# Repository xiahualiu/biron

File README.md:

# biron

Biron is an open source soldering iron hardware based on Baxandall Oscillator. This is a homebrew project that I am doing during the free time at home.

## Software Requirements

* KiCAD v7.0.0 or above to view the schematic and PCB files.
* LTSpice 17.1.6.0 or above to view the SPICE simulation.

## Disclaimer

This is an open source project that involves high voltage and hot surfaces. You must have enough experience to build it in real life and wear PPE, I don't want people get hurt.

This project follows the Ti's [DAQ system requirements](https://www.ti.com/solution/data-acquisition-daq), the control system is fully galvanized isolated from the physical and power signals.

### Power isolation

I used a minimal push-pull converter for the DC/DC part:

### Sensor signal isolation

Sensor signals are amplifier through a TL082H (not practical in the real world because of the high Vos, you want Vos<100uV if possible). The signal is read by a RV1S9353A from Renesas.

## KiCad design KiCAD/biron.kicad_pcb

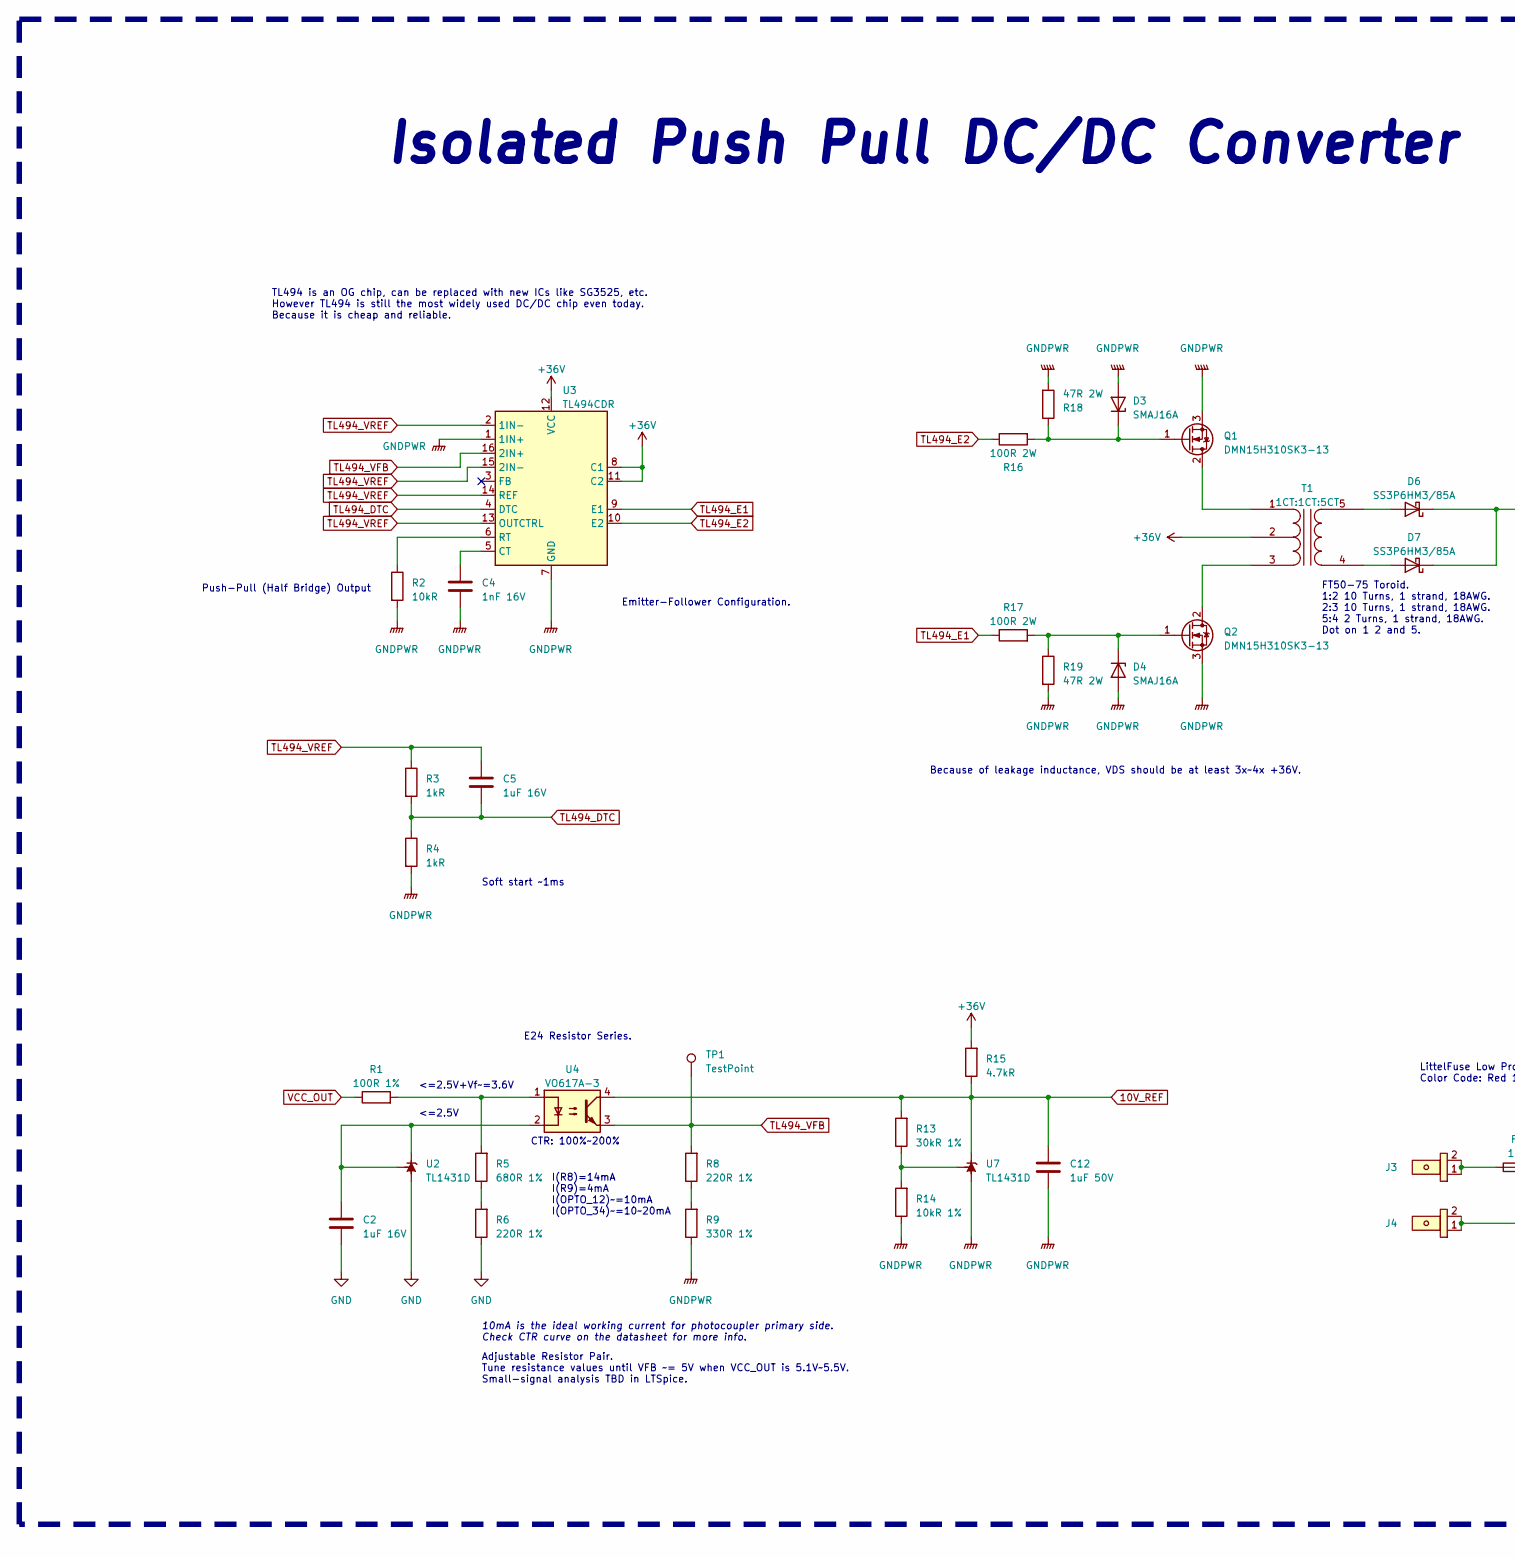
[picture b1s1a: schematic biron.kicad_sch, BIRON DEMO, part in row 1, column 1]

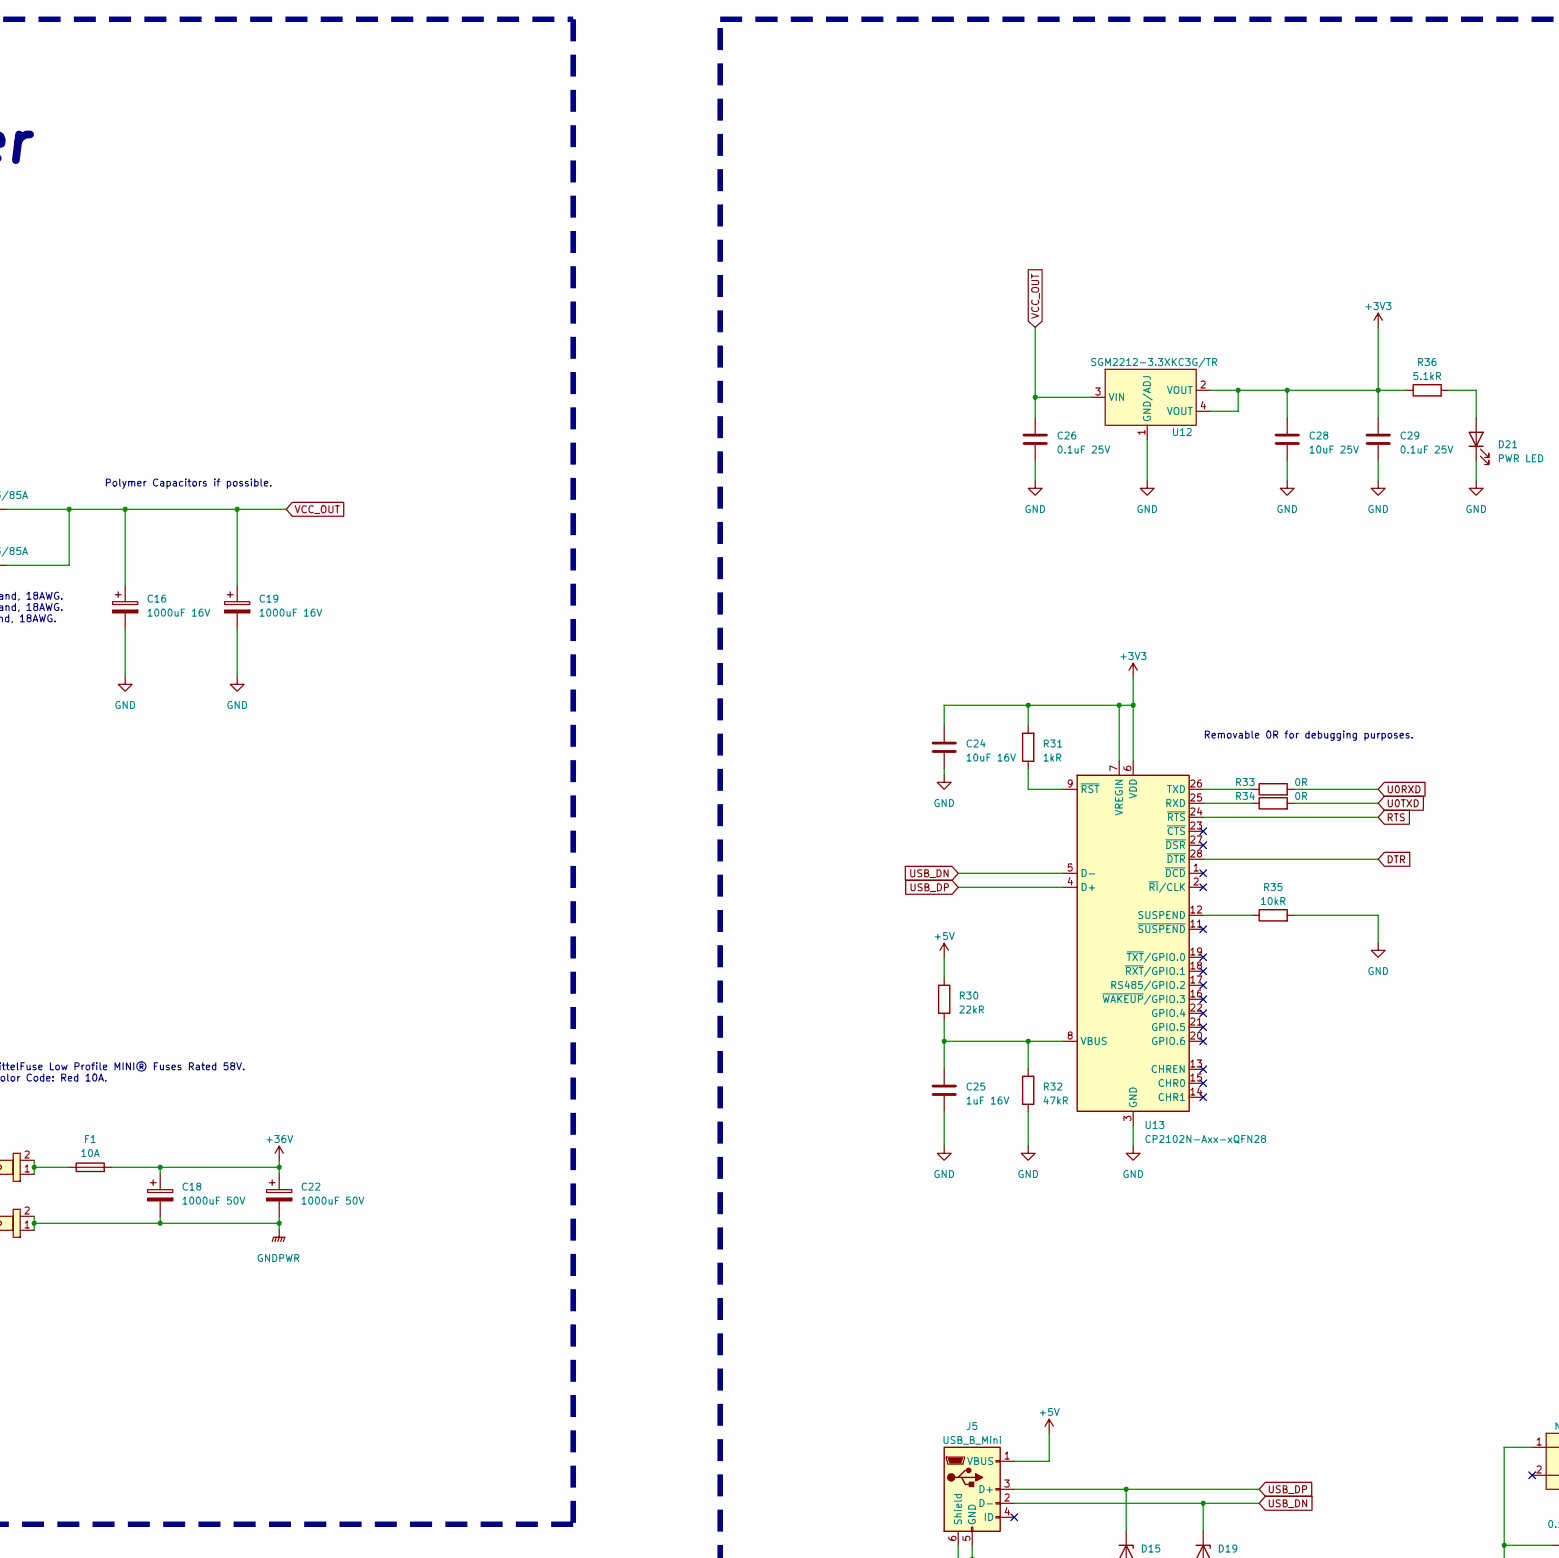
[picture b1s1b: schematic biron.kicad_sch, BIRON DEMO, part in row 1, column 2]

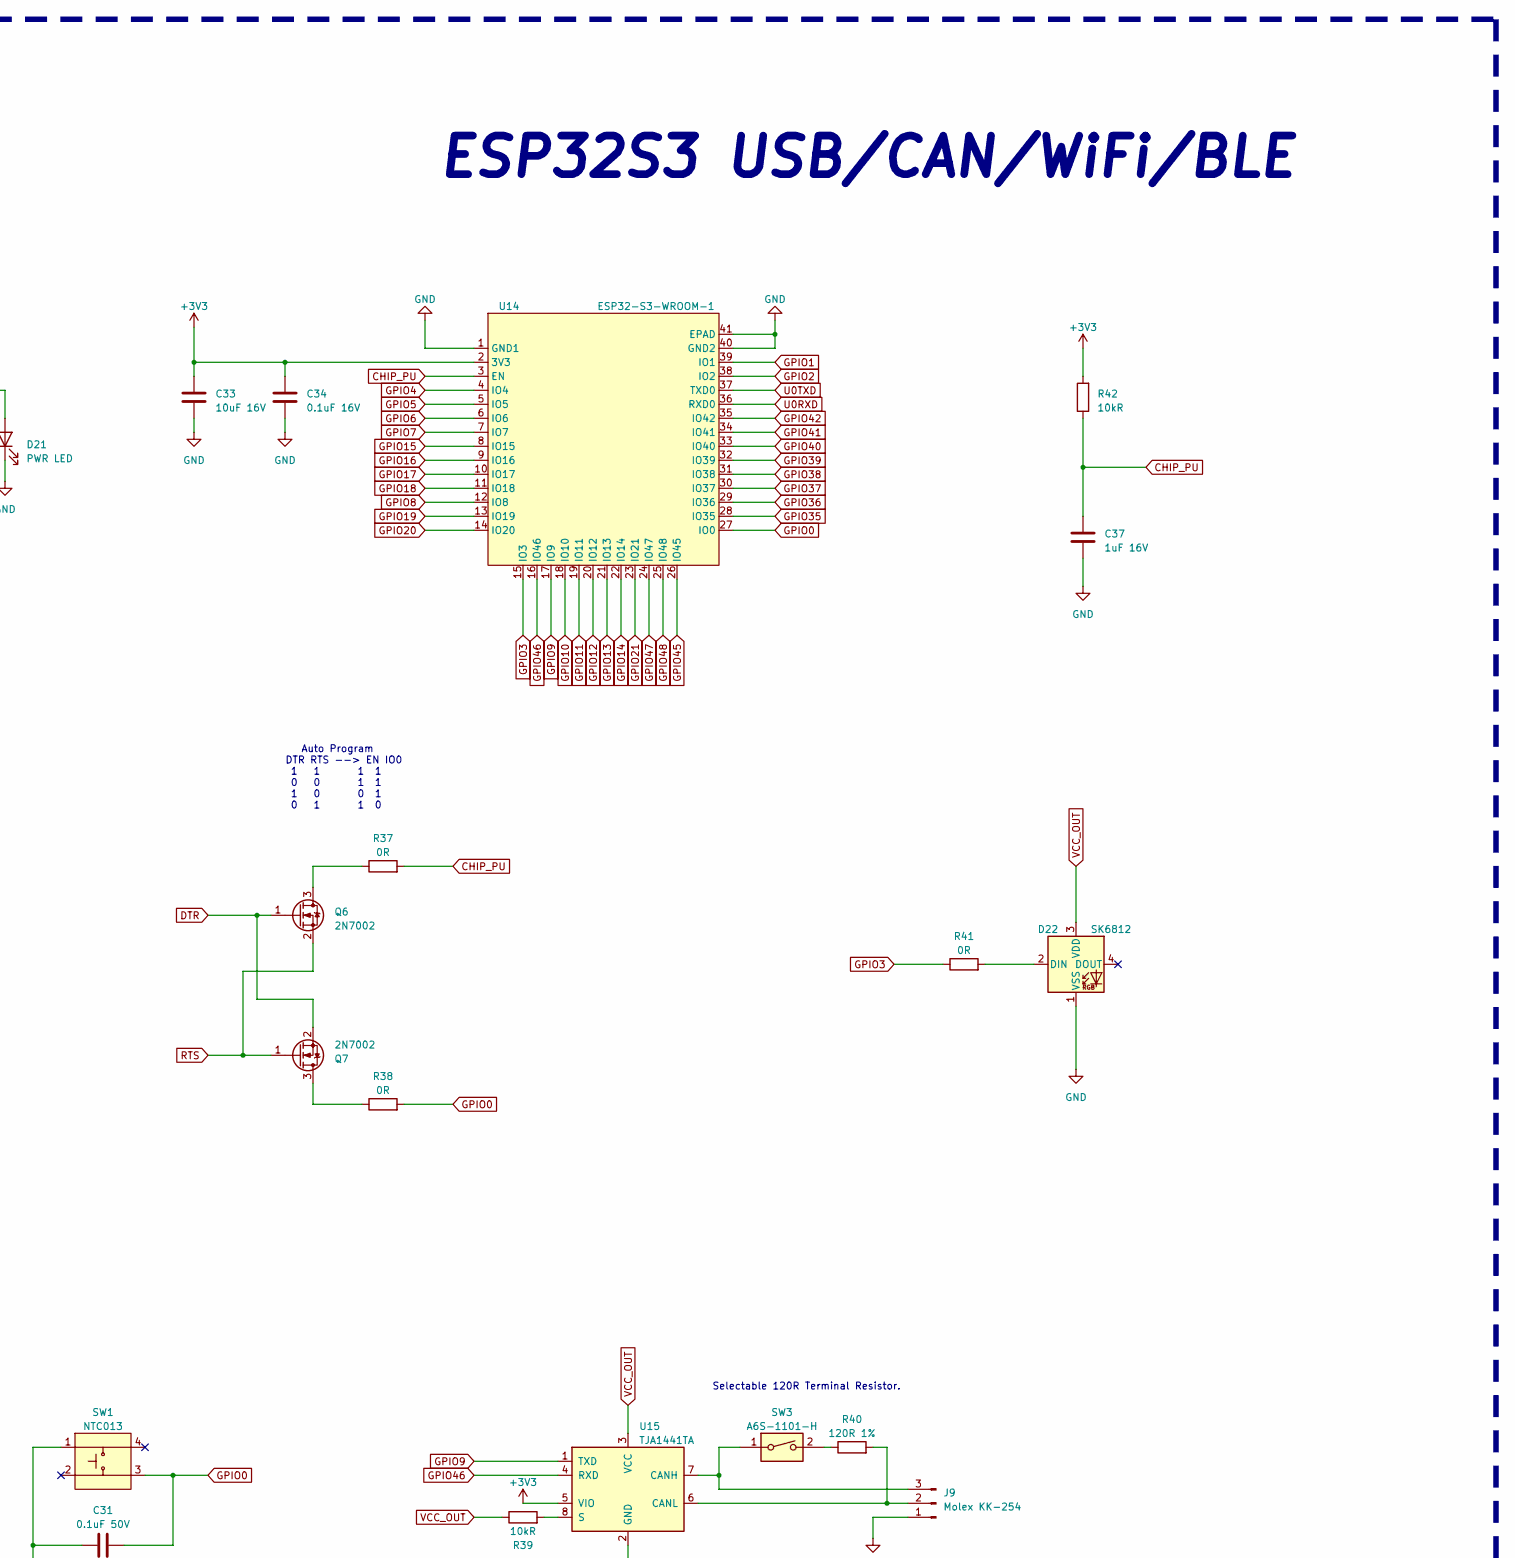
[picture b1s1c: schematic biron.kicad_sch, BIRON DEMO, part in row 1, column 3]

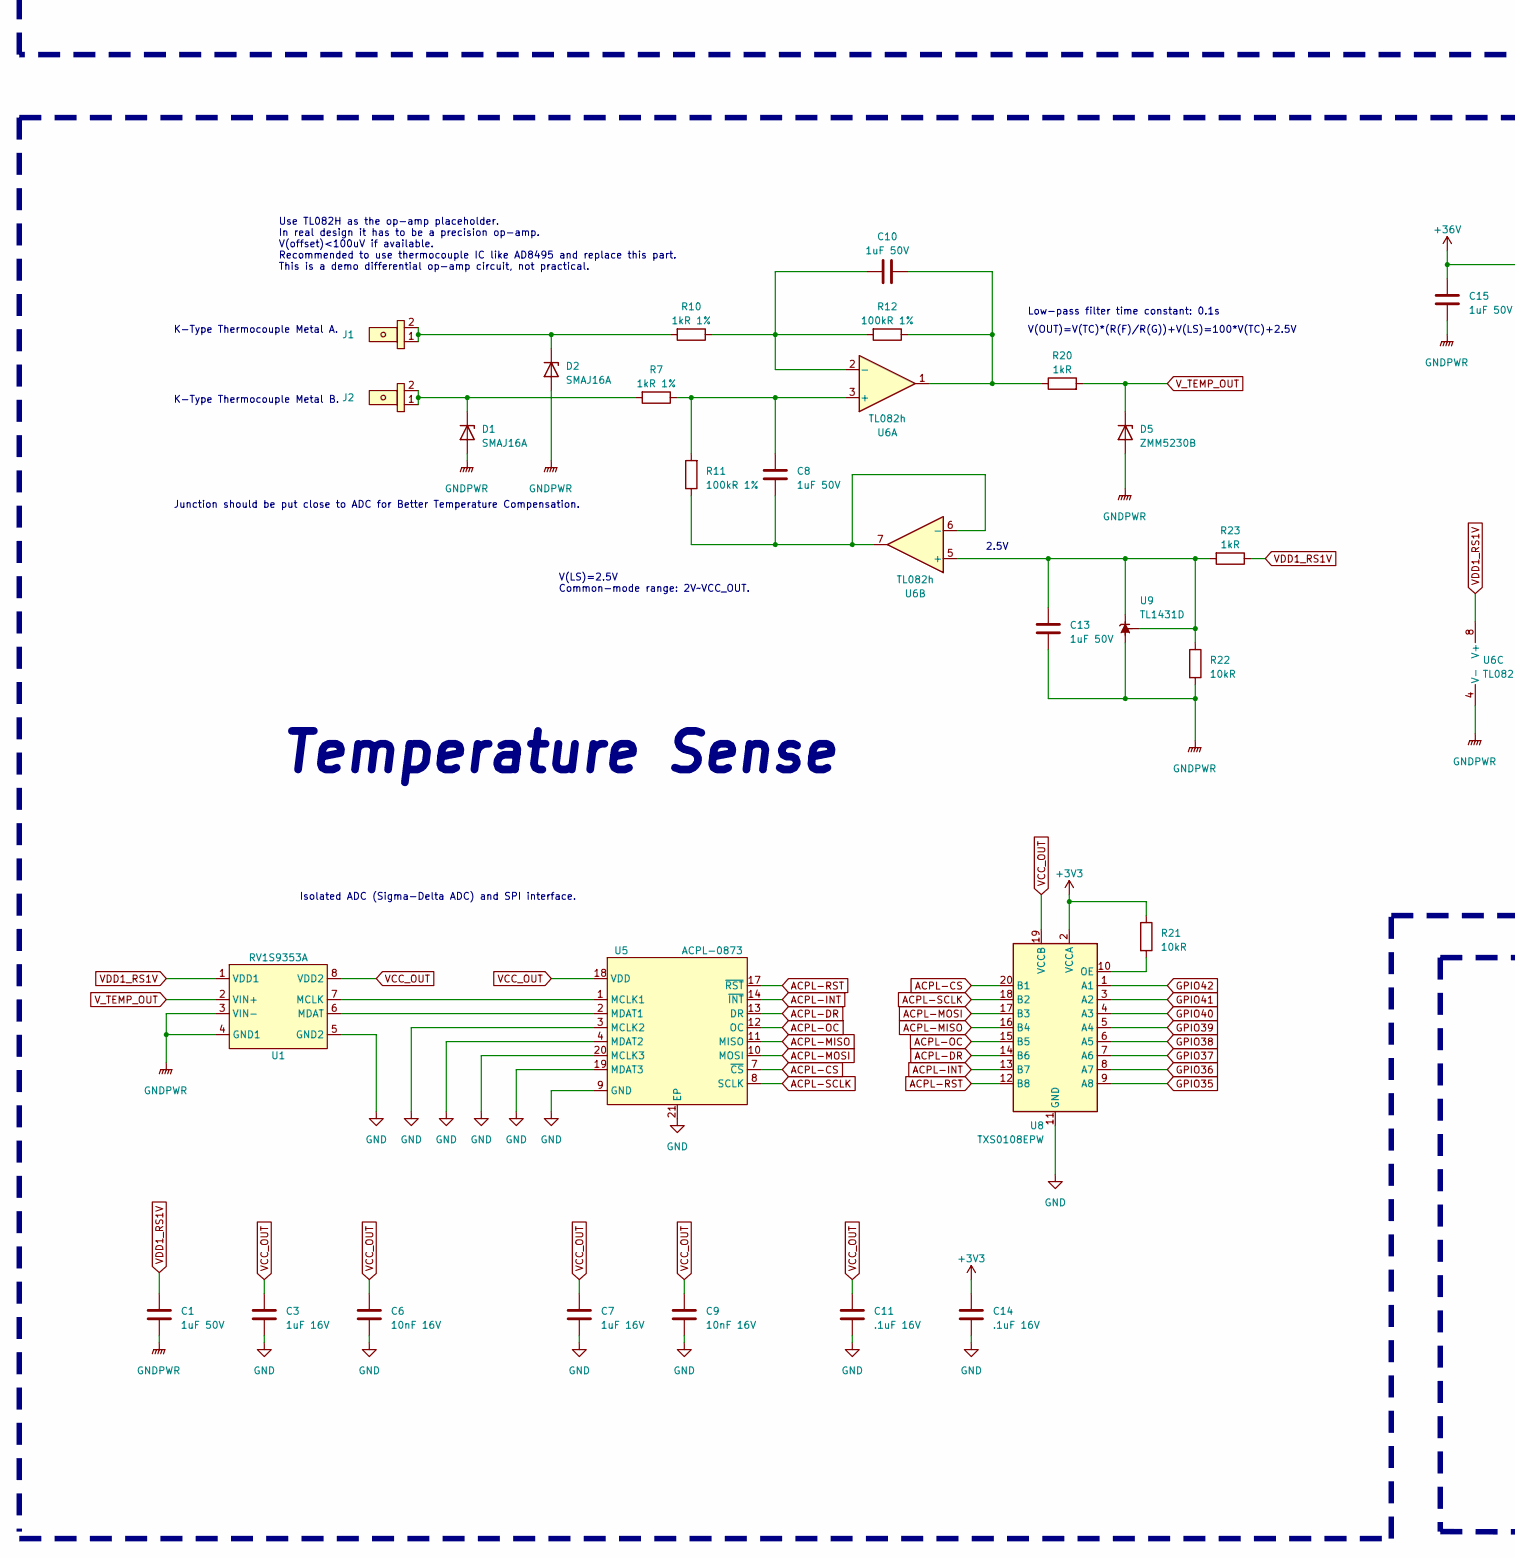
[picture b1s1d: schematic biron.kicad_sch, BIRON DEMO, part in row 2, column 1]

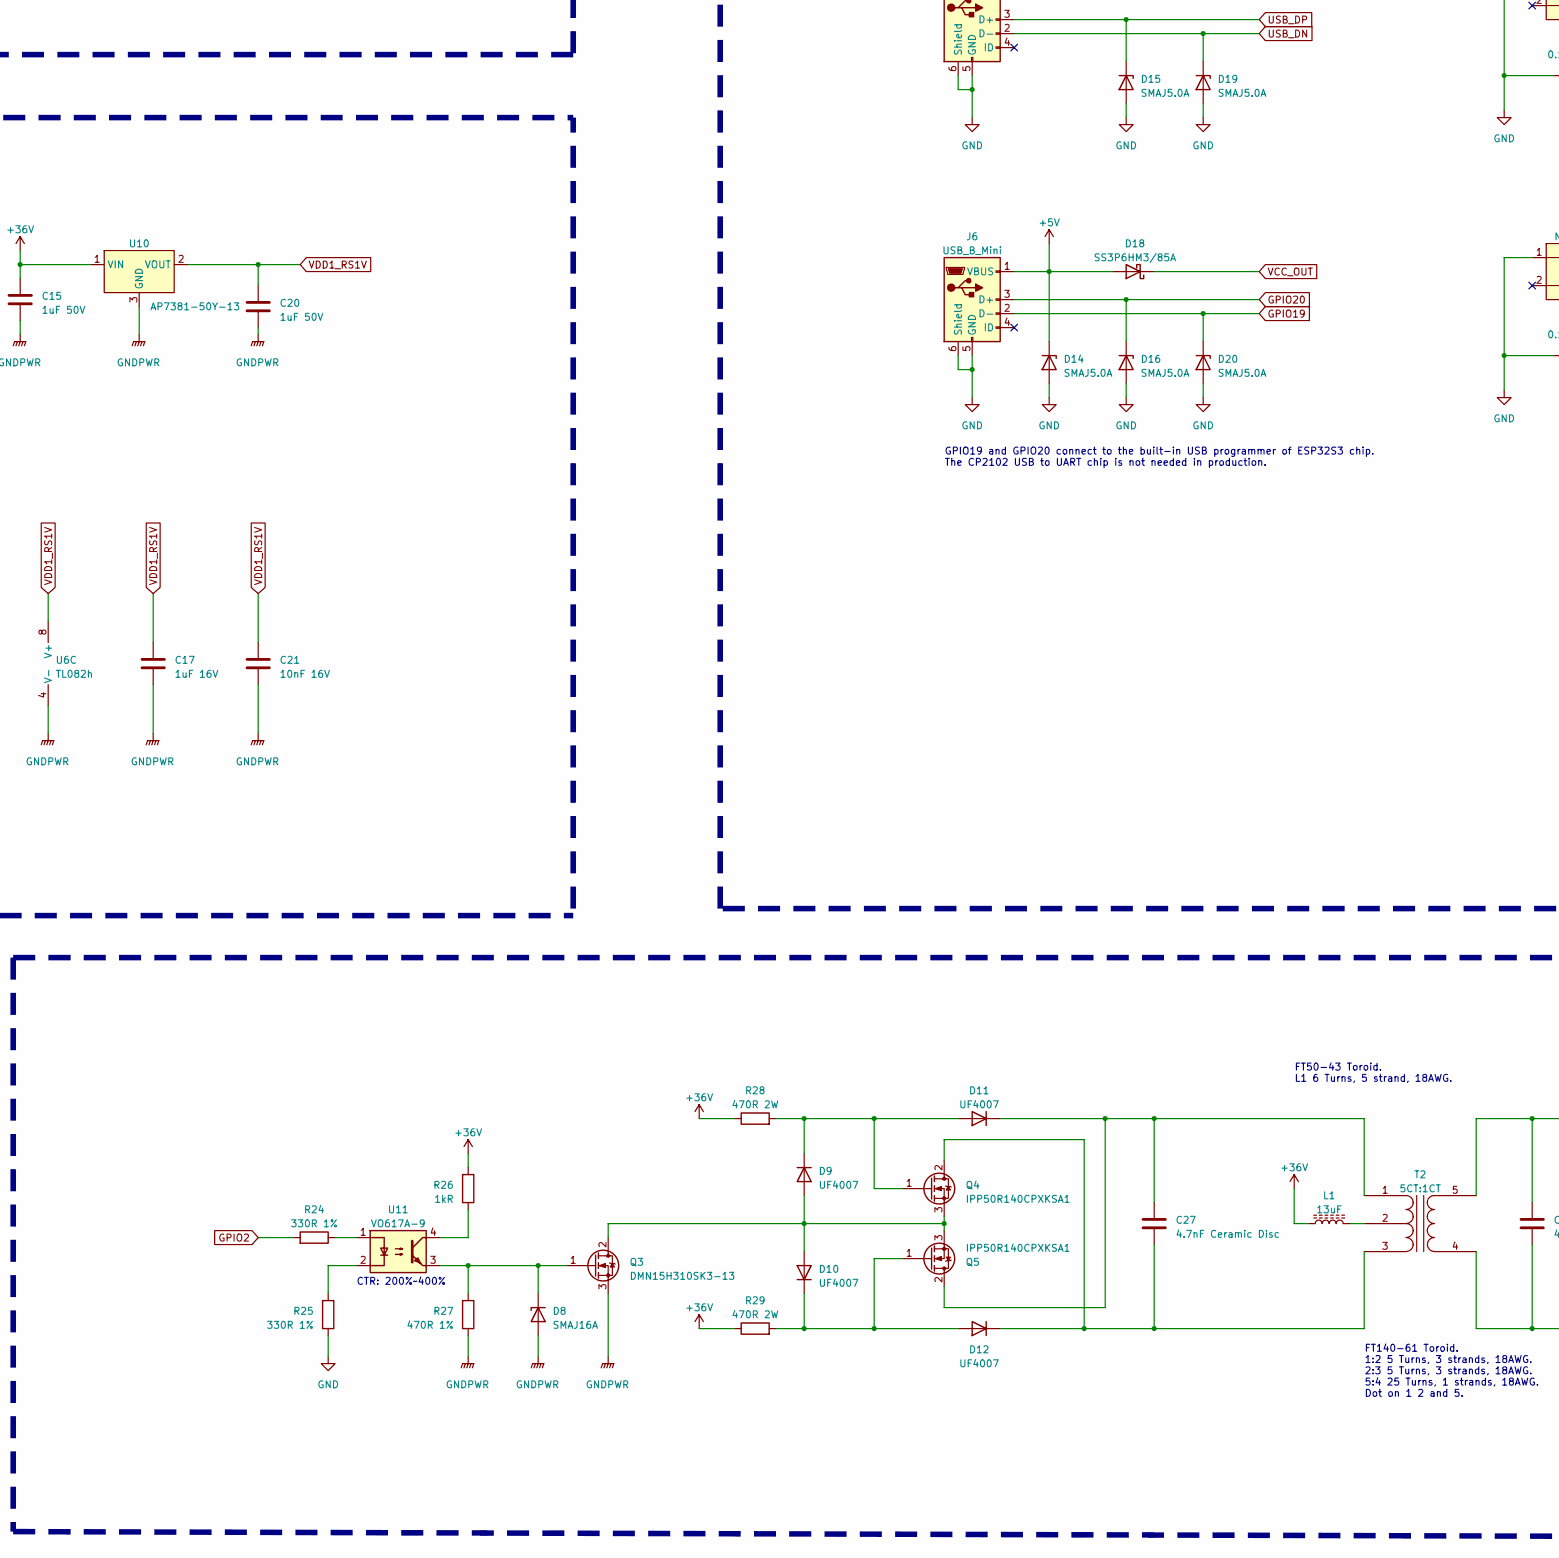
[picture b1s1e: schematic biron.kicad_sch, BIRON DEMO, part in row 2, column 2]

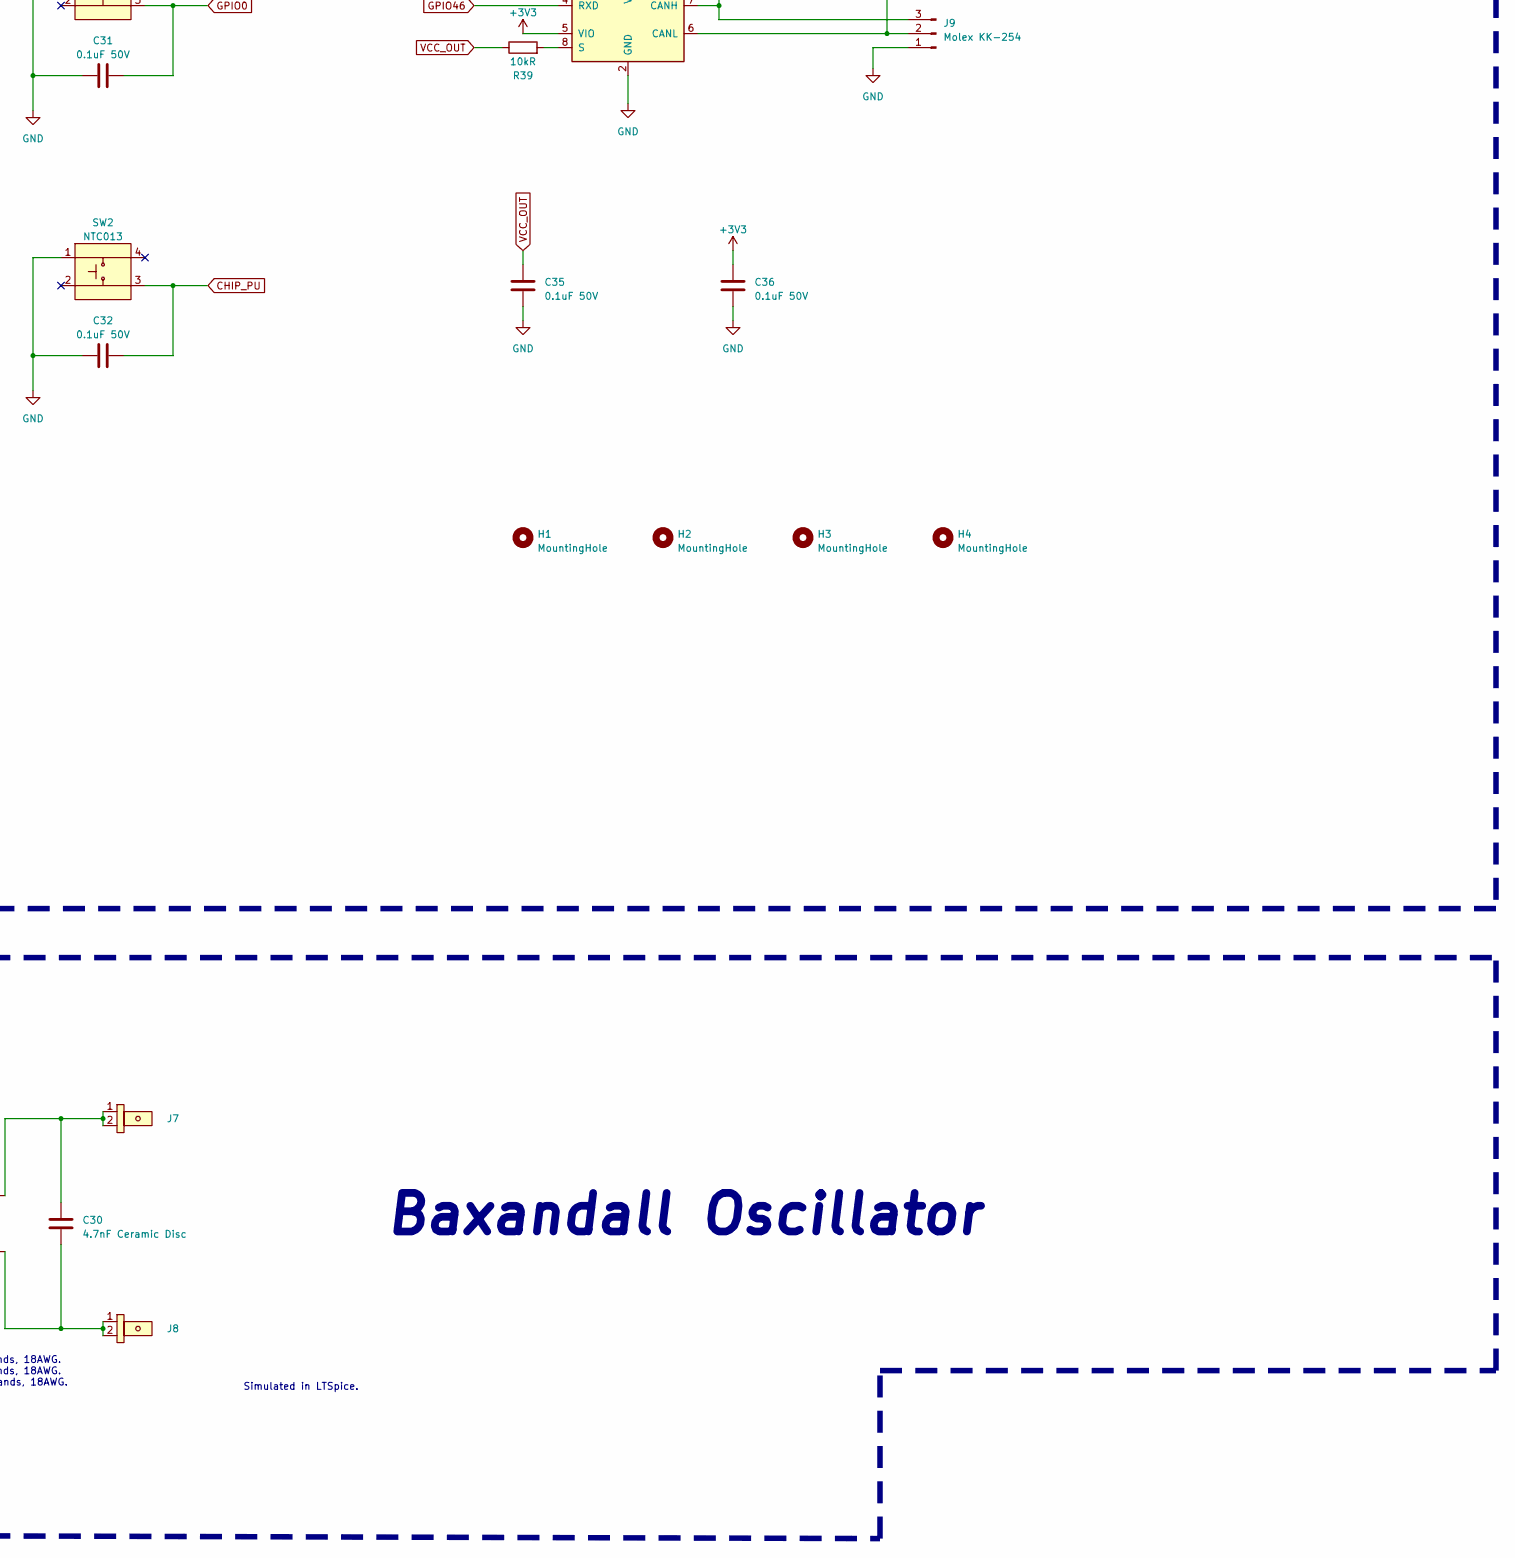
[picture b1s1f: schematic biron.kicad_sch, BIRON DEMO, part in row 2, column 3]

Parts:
C1, C8, C10, C12, C13, C15, C20: 1uF 50V; C_0805_2012Metric_Pad1.18x1.45mm_HandSolder
C2, C25: 1uF 16V; C_0805_2012Metric
C3, C5, C7, C17, C37: 1uF 16V; C_0805_2012Metric_Pad1.18x1.45mm_HandSolder
C4: 1nF 16V; C_0603_1608Metric
C6, C21: 10nF 16V; C_0603_1608Metric
C9: 10nF 16V; C_0805_2012Metric_Pad1.18x1.45mm_HandSolder
C11, C14: .1uF 16V; C_0805_2012Metric_Pad1.18x1.45mm_HandSolder
C16, C19: 1000uF 16V; CP_Elec_10x12.5
C18, C22: 1000uF 50V; CP_Radial_D13.0mm_P5.00mm
C24, C33: 10uF 16V; C_0805_2012Metric
C26: 0.1uF 25V; C_0805_2012Metric_Pad1.18x1.45mm_HandSolder
C27, C30: 4.7nF Ceramic Disc; C_Disc_D11.0mm_W5.0mm_P5.00mm
C28: 10uF 25V; C_0805_2012Metric_Pad1.18x1.45mm_HandSolder
C29: 0.1uF 25V; C_0603_1608Metric
C31, C32, C35, C36: 0.1uF 50V; C_0805_2012Metric_Pad1.18x1.45mm_HandSolder
C34: 0.1uF 16V; C_0402_1005Metric
D1, D2, D3, D4, D8: SMAJ16A; D_SMA
D5: ZMM5230B; D_MiniMELF
D6, D7, D18: SS3P6HM3/85A; DO-220AA
D9, D10, D11, D12: UF4007; D_DO-41_SOD81_P10.16mm_Horizontal
D14, D15, D16, D19, D20: SMAJ5.0A; D_SMA
D21: PWR LED; LED_PLCC-2_3x2mm_KA
D22: SK6812; LED_SK6812_PLCC4_5.0x5.0mm_P3.2mm
F1: 10A; FUSE_3557-2
H1, H2, H3, H4: MountingHole; MountingHole_3mm_Pad_Via
J1, J2, J3, J4, J7, J8: 1217861
J5, J6: USB_B_Mini; USB_Mini-B_Wuerth_65100516121_Horizontal
J9: Molex KK-254; Molex_KK-254_AE-6410-03A_1x03_P2.54mm_Vertical
L1: 13uF; FT50-43
Q1, Q2, Q3: DMN15H310SK3-13; TO-252-3_TabPin2
Q4, Q5: IPP50R140CPXKSA1; TO-220-3_Horizontal_TabDown
Q6, Q7: 2N7002; SOT-23
R1: 100R 1%; C_0805_2012Metric_Pad1.18x1.45mm_HandSolder
R2, R42: 10kR; C_0603_1608Metric
R3, R4, R31: 1kR; R_0603_1608Metric
R5: 680R 1%; C_0805_2012Metric_Pad1.18x1.45mm_HandSolder
R6, R8: 220R 1%; C_0805_2012Metric_Pad1.18x1.45mm_HandSolder
R7, R10: 1kR 1%; R_0603_1608Metric
R9, R24, R25: 330R 1%; C_0805_2012Metric_Pad1.18x1.45mm_HandSolder
R11, R12: 100kR 1%; R_0603_1608Metric
R13: 30kR 1%; C_0805_2012Metric_Pad1.18x1.45mm_HandSolder
R14: 10kR 1%; C_0805_2012Metric_Pad1.18x1.45mm_HandSolder
R15: 4.7kR; C_0805_2012Metric_Pad1.18x1.45mm_HandSolder
R16, R17: 100R 2W; R_2512_6332Metric
R18, R19: 47R 2W; R_2512_6332Metric
R20: 1kR; R_0805_2012Metric
R21, R22: 10kR; C_0805_2012Metric_Pad1.18x1.45mm_HandSolder
R23, R26: 1kR; C_0805_2012Metric_Pad1.18x1.45mm_HandSolder
R27: 470R 1%; C_0805_2012Metric_Pad1.18x1.45mm_HandSolder
R28, R29: 470R 2W; R_2512_6332Metric
R30: 22kR; R_0603_1608Metric
R32: 47kR; R_0603_1608Metric
R33, R34, R37, R38, R41: 0R; R_0603_1608Metric
R35: 10kR; R_0603_1608Metric
R36: 5.1kR; R_0805_2012Metric
R39: 10kR; R_0805_2012Metric
R40: 120R 1%; R_0805_2012Metric
SW1, SW2: NTC013; SW_Push_1P1T_NO_Vertical_Wuerth_434133025816
SW3: A6S-1101-H; SW_DIP_SPSTx01_Slide_Omron_A6S-110x_W8.9mm_P2.54mm
T1: 1CT:1CT:5CT; FT50-75
T2: 5CT:1CT; FT140-61
TP1: TestPoint; TestPoint_Pad_2.0x2.0mm
U1: RV1S9353A
U2, U7, U9: TL1431D; SOIC-8_3.9x4.9mm_P1.27mm
U3: TL494CDR; SOIC-16_3.9x9.9mm_P1.27mm
U4: VO617A-3; DIP-4_W7.62mm
U5: ACPL-0873; QFN-20-1EP_5x5mm_P0.65mm_EP3.35x3.35mm_ThermalVias
U6: TL082h; SOIC-8_3.9x4.9mm_P1.27mm
U8: TXS0108EPW; TSSOP-20_4.4x6.5mm_P0.65mm
U10: AP7381-50Y-13; SOT-89-3
U11: VO617A-9; DIP-4_W7.62mm
U12: SGM2212-3.3XKC3G/TR; SOT-223
U13: CP2102N-Axx-xQFN28; QFN-28-1EP_5x5mm_P0.5mm_EP3.35x3.35mm
U14: ESP32-S3-WROOM-1
U15: TJA1441TA; SOIC-8_3.9x4.9mm_P1.27mm

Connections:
10V_REF: C12.1, R13.2, R15.1, U4.4, U7.1 (K)
+3V3: C14.1, C24.1, C28.1, C29.1, C33.1, C34.1, C36.2, R21.1, R31.2, R36.1, R42.2, U8.2 (VCCA), U12.2 (VOUT), U12.4 (VOUT), U13.6 (VDD), U13.7 (VREGIN), U14.2 (3V3), U15.5 (VIO)
+5V: D14.1 (K), D18.2 (A), J5.1 (VBUS), J6.1 (VBUS), R30.1
+36V: C15.1, C18.1, C22.1, F1.2, L1.1, R15.2, R26.2, R28.1, R29.1, T1.2 (PM), U3.8 (C1), U3.11 (C2), U3.12 (VCC), U10.1 (VIN)
ACPL-CS: U5.7 (~CS), U8.20 (B1)
ACPL-DR: U5.13 (DR), U8.14 (B6)
ACPL-INT: U5.14 (~INT), U8.13 (B7)
ACPL-MISO: U5.11 (MISO), U8.16 (B4)
ACPL-MOSI: U5.10 (MOSI), U8.17 (B3)
ACPL-OC: U5.12 (OC), U8.15 (B5)
ACPL-RST: U5.17 (~RST), U8.12 (B8)
ACPL-SCLK: U5.8 (SCLK), U8.18 (B2)
CHIP_PU: C32.2, C37.1, R37.2, R42.1, SW2.3, U14.3 (EN)
DTR: Q6.1 (G), Q7.2 (S), U13.28 (~DTR)
GND: C2.2, C3.2, C6.2, C7.2, C9.2, C11.2, C14.2, C16.2, C19.2, C24.2, C25.2, C26.2, C28.2, C29.2, C31.1, C32.1, C33.2, C34.2, C35.1, C36.1, C37.2, D14.2 (A), D15.2 (A), D16.2 (A), D19.2 (A), D20.2 (A), D21.1 (K), D22.1 (VSS), J5.5 (GND), J5.6 (Shield), J6.5 (GND), J6.6 (Shield), J9.1, R6.1, R25.1, R32.2, R35.2, SW1.1, SW2.1, U1.5 (GND2), U2.2 (A), U2.3 (A), U2.6 (A), U2.7 (A), U5.3 (MCLK2), U5.4 (MDAT2), U5.9 (GND), U5.19 (MDAT3), U5.20 (MCLK3), U5.21 (EP), U8.11 (GND), U12.1 (GND/ADJ), U13.3 (GND), U13.29 (GND), U14.1 (GND1), U14.40 (GND2), U14.41 (EPAD), U15.2 (GND)
GNDPWR: C1.2, C4.2, C12.2, C13.2, C15.2, C17.2, C18.2, C20.2, C21.2, C22.2, D1.2 (A), D2.2 (A), D3.2 (A), D4.2 (A), D5.2 (A), D8.2 (A), J4.1, J4.2, Q1.3 (S), Q2.3 (S), Q3.3 (S), R2.2, R4.2, R9.1, R14.1, R18.2, R19.2, R22.2, R27.1, U1.3 (VIN-), U1.4 (GND1), U3.1 (1IN+), U3.7 (GND), U6.4 (V-), U7.2 (A), U7.3 (A), U7.6 (A), U7.7 (A), U9.2 (A), U9.3 (A), U9.6 (A), U9.7 (A), U10.3 (GND)
GPIO0: C31.2, R38.2, SW1.3, U14.27 (IO0)
GPIO1: U14.39 (IO1)
GPIO2: R24.2, U14.38 (IO2)
GPIO3: R41.1, U14.15 (IO3)
GPIO4: U14.4 (IO4)
GPIO5: U14.5 (IO5)
GPIO6: U14.6 (IO6)
GPIO7: U14.7 (IO7)
GPIO8: U14.12 (IO8)
GPIO9: U14.17 (IO9), U15.1 (TXD)
GPIO10: U14.18 (IO10)
GPIO11: U14.19 (IO11)
GPIO12: U14.20 (IO12)
GPIO13: U14.21 (IO13)
GPIO14: U14.22 (IO14)
GPIO15: U14.8 (IO15)
GPIO16: U14.9 (IO16)
GPIO17: U14.10 (IO17)
GPIO18: U14.11 (IO18)
GPIO19: D20.1 (K), J6.2 (D-), U14.13 (IO19)
GPIO20: D16.1 (K), J6.3 (D+), U14.14 (IO20)
GPIO21: U14.23 (IO21)
GPIO35: U8.9 (A8), U14.28 (IO35)
GPIO36: U8.8 (A7), U14.29 (IO36)
GPIO37: U8.7 (A6), U14.30 (IO37)
GPIO38: U8.6 (A5), U14.31 (IO38)
GPIO39: U8.5 (A4), U14.32 (IO39)
GPIO40: U8.4 (A3), U14.33 (IO40)
GPIO41: U8.3 (A2), U14.34 (IO41)
GPIO42: U8.1 (A1), U14.35 (IO42)
GPIO45: U14.26 (IO45)
GPIO46: U14.16 (IO46), U15.4 (RXD)
GPIO47: U14.24 (IO47)
GPIO48: U14.25 (IO48)
unnamed: C10.2, R12.1, R20.1, U6.1
unnamed: D1.1 (K), J2.1, J2.2, R7.2
unnamed: D2.1 (K), J1.1, J1.2, R10.2
unnamed: D3.1 (K), Q1.1 (G), R16.2, R18.1
unnamed: D4.1 (K), Q2.1 (G), R17.2, R19.1
unnamed: D6.2 (A), T1.5 (S2)
unnamed: D7.2 (A), T1.4 (S1)
unnamed: D8.1 (K), Q3.1 (G), R27.2, U11.3
unnamed: D9.2 (A), D10.2 (A), Q3.2 (D), Q4.3 (S), Q5.3 (S)
unnamed: D10.1 (K), D12.2 (A), Q5.1 (G), R29.2
unnamed: D9.1 (K), D11.2 (A), Q4.1 (G), R28.2
unnamed: C27.1, D11.1 (K), Q5.2 (D), T2.1 (PR1)
unnamed: C27.2, D12.1 (K), Q4.2 (D), T2.3 (PR2)
unnamed: D21.2 (A), R36.2
unnamed: D22.2 (DIN), R41.2
unnamed: F1.1, J3.1, J3.2
unnamed: J9.2, R40.2, U15.6 (CANL)
unnamed: J9.3, SW3.1, U15.7 (CANH)
unnamed: Q1.2 (D), T1.1 (PR1)
unnamed: Q2.2 (D), T1.3 (PR2)
unnamed: Q6.3 (D), R37.1
unnamed: Q7.3 (D), R38.1
unnamed: R1.2, R5.2, U4.1
unnamed: R5.1, R6.2
unnamed: R8.1, R9.2
unnamed: R24.1, U11.1
unnamed: R25.2, U11.2
unnamed: R26.1, U11.4
unnamed: R40.1, SW3.2
unnamed: L1.2, T2.2 (PM)
unnamed: C30.2, J8.1, J8.2, T2.4 (S1)
unnamed: C30.1, J7.1, J7.2, T2.5 (S2)
unnamed: U1.7 (MCLK), U5.1 (MCLK1)
unnamed: U1.6 (MDAT), U5.2 (MDAT1)
unnamed: C2.1, U2.1 (K), U2.8 (REF), U4.2
unnamed: C4.1, U3.5 (CT)
unnamed: R2.1, U3.6 (RT)
unnamed: C8.1, R7.1, R11.2, U6.3 (+)
unnamed: C10.1, R10.1, R12.2, U6.2 (-)
unnamed: C13.1, R22.1, R23.2, U6.5 (+), U9.1 (K), U9.8 (REF)
unnamed: C8.2, R11.1, U6.6 (-), U6.7
unnamed: R13.1, R14.2, U7.8 (REF)
unnamed: R21.2, U8.10 (OE)
unnamed: R34.1, U13.25 (RXD)
unnamed: R35.1, U13.12 (SUSPEND)
unnamed: R33.1, U13.26 (TXD)
unnamed: C25.1, R30.2, R32.1, U13.8 (VBUS)
unnamed: R31.1, U13.9 (~RST)
unnamed: R39.2, U15.8 (S)
RTS: Q6.2 (S), Q7.1 (G), U13.24 (~RTS)
TL494_DTC: C5.2, R3.2, R4.1, U3.4 (DTC)
TL494_E1: R17.1, U3.9 (E1)
TL494_E2: R16.1, U3.10 (E2)
TL494_VFB: R8.2, TP1.1, U3.16 (2IN+), U4.3
TL494_VREF: C5.1, R3.1, U3.2 (1IN-), U3.13 (OUTCTRL), U3.14 (REF), U3.15 (2IN-)
U0RXD: R33.2, U14.36 (RXD0)
U0TXD: R34.2, U14.37 (TXD0)
USB_DN: D19.1 (K), J5.2 (D-), U13.5 (D-)
USB_DP: D15.1 (K), J5.3 (D+), U13.4 (D+)
VCC_OUT: C3.1, C6.1, C7.1, C9.1, C11.1, C16.1, C19.1, C26.1, C35.2, D6.1 (K), D7.1 (K), D18.1 (K), D22.3 (VDD), R1.1, R39.1, U1.8 (VDD2), U5.18 (VDD), U8.19 (VCCB), U12.3 (VIN), U15.3 (VCC)
VDD1_RS1V: C1.1, C17.1, C20.1, C21.1, R23.1, U1.1 (VDD1), U6.8 (V+), U10.2 (VOUT)
V_TEMP_OUT: D5.1 (K), R20.2, U1.2 (VIN+)

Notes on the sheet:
FT50-75 Toroid. 1:2 10 Turns, 1 strand, 18AWG. 2:3 10 Turns, 1 strand, 18AWG. 5:4 2 Turns, 1 strand, 18AWG. Dot on 1 2 and 5.
Low-pass filter time constant: 0.1s
GPIO19 and GPIO20 connect to the built-in USB programmer of ESP32S3 chip. The CP2102 USB to UART chip is not needed in production.
Adjustable Resistor Pair. Tune resistance values until VFB ~= 5V when VCC_OUT is 5.1V~5.5V. Small-signal analysis TBD in LTSpice.
Selectable 120R Terminal Resistor.
V(LS)=2.5V Common-mode range: 2V~VCC_OUT.
Push-Pull (Half Bridge) Output
CTR: 200%~400%
Junction should be put close to ADC for Better Temperature Compensation.
CTR: 100%~200%
TL494 is an OG chip, can be replaced with new ICs like SG3525, etc. However TL494 is still the most widely used DC/DC chip even today. Because it is cheap and reliable.
E24 Resistor Series.
Because of leakage inductance, VDS should be at least 3x~4x +36V.
Removable 0R for debugging purposes.
Isolated ADC (Sigma-Delta ADC) and SPI interface.
Simulated in LTSpice.
10mA is the ideal working current for photocoupler primary side. Check CTR curve on the datasheet for more info.
Emitter-Follower Configuration.
K-Type Thermocouple Metal A.
ESP32S3 USB/CAN/WiFi/BLE
<=2.5V+Vf~=3.6V
FT50-43 Toroid. L1 6 Turns, 5 strand, 18AWG.
FT140-61 Toroid. 1:2 5 Turns, 3 strands, 18AWG. 2:3 5 Turns, 3 strands, 18AWG. 5:4 25 Turns, 1 strands, 18AWG. Dot on 1 2 and 5.
Temperature Sense
LittelFuse Low Profile MINI® Fuses Rated 58V. Color Code: Red 10A.
<=2.5V
Soft start ~1ms
V(OUT)=V(TC)*(R(F)/R(G))+V(LS)=100*V(TC)+2.5V
Baxandall Oscillator
Auto Program DTR RTS --> EN IO0 1 1 1 1 0 0 1 1 1 0 0 1 0 1 1 0
Use TL082H as the op-amp placeholder. In real design it has to be a precision op-amp. V(offset)<100uV if available. Recommended to use thermocouple IC like AD8495 and replace this part. This is a demo differential op-amp circuit, not practical.
2.5V
Isolated Push Pull DC/DC Converter
I(R8)=14mA I(R9)=4mA I(OPTO_12)~=10mA I(OPTO_34)~=10~20mA
Polymer Capacitors if possible.
K-Type Thermocouple Metal B.

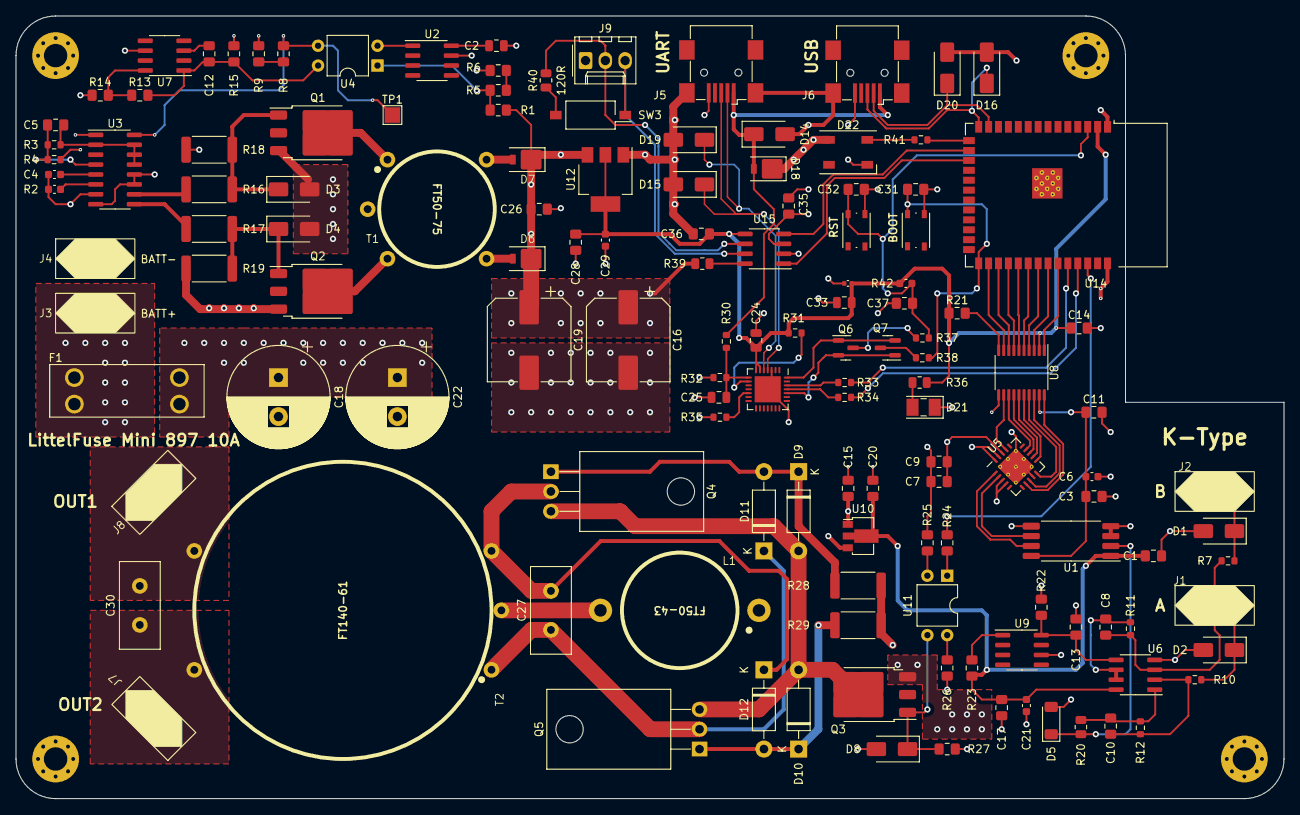
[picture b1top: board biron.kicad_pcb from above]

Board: 4 copper layers, 162.6 x 100.3 mm, 141 parts (0 on the bottom side), 93 nets.

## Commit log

2023-02-08 Update ltspice
2023-03-25 Update PCB
2023-03-25 Update Text
2023-03-25 Update PCB silkscreen

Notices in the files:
KiCAD/biron.kicad_sch:
Project is under CC0 license, feel free to use it!
